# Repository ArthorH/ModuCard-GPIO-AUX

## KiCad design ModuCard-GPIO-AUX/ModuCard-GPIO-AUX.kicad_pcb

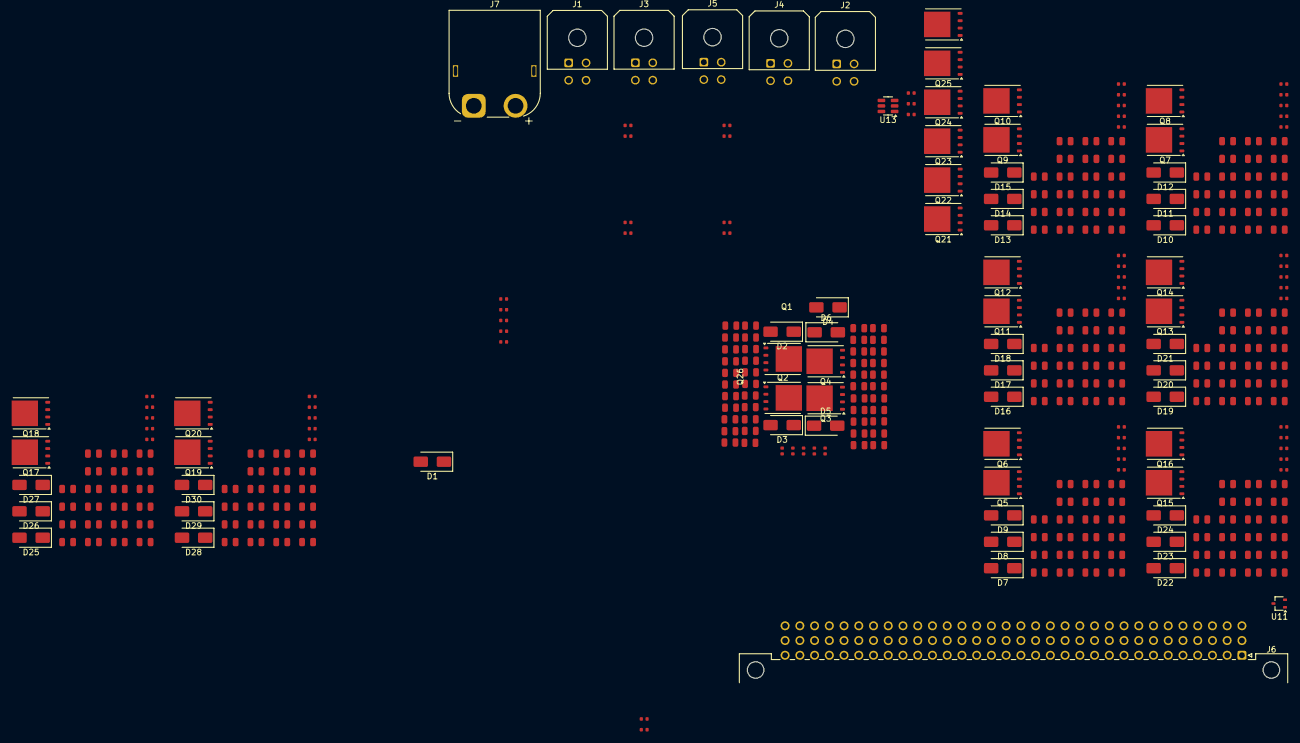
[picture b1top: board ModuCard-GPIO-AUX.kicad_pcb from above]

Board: 2 copper layers, 348 parts (0 on the bottom side), 159 nets, no tracks yet.

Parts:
C1, C2, C3, C4, C5, C6, C7, C8, C9, C10, C11, C12, C13, C14, C15, C16, C17, C18, C19, C20, C21, C22, C23, C24, C25, C26, C27, C28, C29, C30, C31, C32, C33, C34, C35, C36, C37, C38, C39, C40, C41, C42, C43, C44, C45, C46, C47, C48, C49, C50, C51, C52, C53, C54, C55, C56, C57, C58, C59, C60, C61, C62, C63, C64, C65, C66, C67, C68, C69, C70, C71, C72, C73, C74, C75, C76, C77, C78, C79, C80, C81, C82, C83, C84, C85, C86, C87, C88, C89, C90, C91, C92, C93, C94, C95, C96, C97, C98, C99, C100, C101, C102, C103, C104, C105, C106, C107, C108, C109, C110, C111, C112, C113, C114, C115, C116, C117, C118, C119, C120, C121, C122, C123, C124, C125, C126, C127, C128, C129, C130, C131, C132, C133, C134, C135, C136, C137, C138, C139, C140, C141, C142, C143, C144, C145, C146, C147, C148, C149, C150, C151, C152, C153, C154, C155, C156, C157, C158, C159, C160, C161, C162, C163, C164, C165, C166, C167, C168, C169, C170, C171, C172, C173, C174, C175, C176, C177, C178, C179, C180, C181, C182, C183, C184, C185, C186, C187, C188, C189, C190, C191, C192, C193, C194, C195, C196, C197, C198, C199, C200, C201, C202, C203, C204, C205, C206, C207, C208, C209, C210, C211, C212, C213, C214, C215, C216, C217, C218, C219, C220: 10uF; C_0805
C222, C223: 100nF; C_0402
D1, D2, D3, D4, D5, D6, D7, D8, D9, D10, D11, D12, D13, D14, D15, D16, D17, D18, D19, D20, D21, D22, D23, D24, D25, D26, D27, D28, D29, D30: SS38; D_SMA
J1, J2, J3, J4, J5: Molex_Micro-Fit_3.0 2x2; Molex_Micro-Fit_3.0_43045-0400_2x02_P3.00mm_Horizontal
J6: 09031967921; DIN41612_R_3x32_Female_Horizontal_THT
J7: AMASS XT60; AMASS_XT60PW-M_1x02_P7.20mm_Horizontal
Q1, Q2, Q3, Q4, Q5, Q6, Q7, Q8, Q9, Q10, Q11, Q12, Q13, Q14, Q15, Q16, Q17, Q18, Q19, Q20, Q21, Q22, Q23, Q24, Q25, Q26: XR30N06F; TDSON-8-1
R1, R13, R25, R37, R49: 1kΩ; R_0402
R2, R3, R4, R5, R6, R7, R8, R9, R10, R11, R12, R14, R15, R16, R17, R18, R19, R20, R21, R22, R23, R24, R26, R27, R28, R29, R30, R31, R32, R33, R34, R35, R36, R38, R39, R40, R41, R42, R43, R44, R45, R46, R47, R48, R50, R51, R52, R53, R54, R55, R56, R57, R58, R59, R60, R61: 10kΩ; R_0402
U11: TPD2E2U06DCK; SOT-323_SC-70
U13: LM74700; SOT-23-6

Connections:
+5V: J1.4, J2.4, J3.4, J4.4, J5.4
+5V_STDBY: J6.a3, J6.b3, J6.c3
+12V: J6.a11, J6.a12, J6.b11, J6.b12, J6.c11, J6.c12
+24V: J6.a14, J6.b14, J6.c14
/Conn1/A_OUT: R1.2, R2.2
/Conn1/HalfBridge1/OUT: C44.2, D5.2 (A), D6.1 (K), J1.2, Q3.1 (S), Q3.2 (S), Q3.3 (S), Q4.5 (D)
/Conn1/HalfBridge/OUT: C22.2, D2.2 (A), D3.1 (K), J1.1, Q1.1 (S), Q1.2 (S), Q1.3 (S), Q2.5 (D)
/Conn2/A_OUT: R13.2, R14.2
/Conn2/HalfBridge1/OUT: C66.2, D8.2 (A), D9.1 (K), J2.2, Q5.1 (S), Q5.2 (S), Q5.3 (S), Q6.5 (D)
/Conn2/HalfBridge/OUT: C88.2, D11.2 (A), D12.1 (K), J2.1, Q7.1 (S), Q7.2 (S), Q7.3 (S), Q8.5 (D)
/Conn3/A_OUT: R25.2, R26.2
/Conn3/HalfBridge1/OUT: C110.2, D14.2 (A), D15.1 (K), J3.2, Q9.1 (S), Q9.2 (S), Q9.3 (S), Q10.5 (D)
/Conn3/HalfBridge/OUT: C132.2, D17.2 (A), D18.1 (K), J3.1, Q11.1 (S), Q11.2 (S), Q11.3 (S), Q12.5 (D)
/Conn4/A_OUT: R37.2, R38.2
/Conn4/HalfBridge1/OUT: C154.2, D20.2 (A), D21.1 (K), J4.2, Q13.1 (S), Q13.2 (S), Q13.3 (S), Q14.5 (D)
/Conn4/HalfBridge/OUT: C176.2, D23.2 (A), D24.1 (K), J4.1, Q15.1 (S), Q15.2 (S), Q15.3 (S), Q16.5 (D)
/Conn5/A_OUT: R49.2, R50.2
/Conn5/HalfBridge1/OUT: C198.2, D26.2 (A), D27.1 (K), J5.2, Q17.1 (S), Q17.2 (S), Q17.3 (S), Q18.5 (D)
/Conn5/HalfBridge/OUT: C220.2, D29.2 (A), D30.1 (K), J5.1, Q19.1 (S), Q19.2 (S), Q19.3 (S), Q20.5 (D)
/backplane/BACKPLANE.D+: J6.a2, U11.2
/backplane/BACKPLANE.D-: J6.c2, U11.1
/backplane/CAN1.+: J6.a5, J6.b5, J6.c5
/backplane/CAN1.-: J6.a6, J6.b6, J6.c6
/backplane/CAN2.+: J6.a8, J6.b8, J6.c8
/backplane/CAN2.-: J6.a9, J6.b9, J6.c9
GND: C1.2, C3.2, C5.2, C7.2, C9.2, C11.2, C13.2, C15.2, C17.2, C19.2, C21.2, C23.2, C25.2, C27.2, C29.2, C31.2, C33.2, C35.2, C37.2, C39.2, C41.2, C43.2, C45.2, C47.2, C49.2, C51.2, C53.2, C55.2, C57.2, C59.2, C61.2, C63.2, C65.2, C67.2, C69.2, C71.2, C73.2, C75.2, C77.2, C79.2, C81.2, C83.2, C85.2, C87.2, C89.2, C91.2, C93.2, C95.2, C97.2, C99.2, C101.2, C103.2, C105.2, C107.2, C109.2, C111.2, C113.2, C115.2, C117.2, C119.2, C121.2, C123.2, C125.2, C127.2, C129.2, C131.2, C133.2, C135.2, C137.2, C139.2, C141.2, C143.2, C145.2, C147.2, C149.2, C151.2, C153.2, C155.2, C157.2, C159.2, C161.2, C163.2, C165.2, C167.2, C169.2, C171.2, C173.2, C175.2, C177.2, C179.2, C181.2, C183.2, C185.2, C187.2, C189.2, C191.2, C193.2, C195.2, C197.2, C199.2, C201.2, C203.2, C205.2, C207.2, C209.2, C211.2, C213.2, C215.2, C217.2, C219.2, D3.2 (A), D6.2 (A), D9.2 (A), D12.2 (A), D15.2 (A), D18.2 (A), D21.2 (A), D24.2 (A), D27.2 (A), D30.2 (A), J6.a1, J6.a4, J6.a7, J6.a10, J6.a13, J6.a15, J6.a32, J6.b1, J6.b2, J6.b4, J6.b7, J6.b10, J6.b13, J6.b15, J6.b32, J6.c1, J6.c4, J6.c7, J6.c10, J6.c13, J6.c15, J6.c32, J7.1, Q2.1 (S), Q2.2 (S), Q2.3 (S), Q4.1 (S), Q4.2 (S), Q4.3 (S), Q6.1 (S), Q6.2 (S), Q6.3 (S), Q8.1 (S), Q8.2 (S), Q8.3 (S), Q10.1 (S), Q10.2 (S), Q10.3 (S), Q12.1 (S), Q12.2 (S), Q12.3 (S), Q14.1 (S), Q14.2 (S), Q14.3 (S), Q16.1 (S), Q16.2 (S), Q16.3 (S), Q18.1 (S), Q18.2 (S), Q18.3 (S), Q20.1 (S), Q20.2 (S), Q20.3 (S), R2.1, R5.1, R10.1, R14.1, R17.1, R22.1, R26.1, R29.1, R34.1, R38.1, R41.1, R46.1, R50.1, R53.1, R58.1, U11.3, U13.2 (GND)
unnamed: C2.2, C3.1
unnamed: C4.2, C5.1
unnamed: C6.2, C7.1
unnamed: C8.2, C9.1
unnamed: C10.2, C11.1
unnamed: C12.2, C13.1
unnamed: C14.2, C15.1
unnamed: C16.2, C17.1
unnamed: C18.2, C19.1
unnamed: C20.2, C21.1
unnamed: C24.2, C25.1
unnamed: C26.2, C27.1
unnamed: C28.2, C29.1
unnamed: C30.2, C31.1
unnamed: C32.2, C33.1
unnamed: C34.2, C35.1
unnamed: C36.2, C37.1
unnamed: C38.2, C39.1
unnamed: C40.2, C41.1
unnamed: C42.2, C43.1
unnamed: C46.2, C47.1
unnamed: C48.2, C49.1
unnamed: C50.2, C51.1
unnamed: C52.2, C53.1
unnamed: C54.2, C55.1
unnamed: C56.2, C57.1
unnamed: C58.2, C59.1
unnamed: C60.2, C61.1
unnamed: C62.2, C63.1
unnamed: C64.2, C65.1
unnamed: C68.2, C69.1
unnamed: C70.2, C71.1
unnamed: C72.2, C73.1
unnamed: C74.2, C75.1
unnamed: C76.2, C77.1
unnamed: C78.2, C79.1
unnamed: C80.2, C81.1
unnamed: C82.2, C83.1
unnamed: C84.2, C85.1
unnamed: C86.2, C87.1
unnamed: C90.2, C91.1
unnamed: C92.2, C93.1
unnamed: C94.2, C95.1
unnamed: C96.2, C97.1
unnamed: C98.2, C99.1
unnamed: C100.2, C101.1
unnamed: C102.2, C103.1
unnamed: C104.2, C105.1
unnamed: C106.2, C107.1
unnamed: C108.2, C109.1
unnamed: C112.2, C113.1
unnamed: C114.2, C115.1
unnamed: C116.2, C117.1
unnamed: C118.2, C119.1
unnamed: C120.2, C121.1
unnamed: C122.2, C123.1
unnamed: C124.2, C125.1
unnamed: C126.2, C127.1
unnamed: C128.2, C129.1
unnamed: C130.2, C131.1
unnamed: C134.2, C135.1
unnamed: C136.2, C137.1
unnamed: C138.2, C139.1
unnamed: C140.2, C141.1
unnamed: C142.2, C143.1
unnamed: C144.2, C145.1
unnamed: C146.2, C147.1
unnamed: C148.2, C149.1
unnamed: C150.2, C151.1
unnamed: C152.2, C153.1
unnamed: C156.2, C157.1
unnamed: C158.2, C159.1
unnamed: C160.2, C161.1
unnamed: C162.2, C163.1
unnamed: C164.2, C165.1
unnamed: C166.2, C167.1
unnamed: C168.2, C169.1
unnamed: C170.2, C171.1
unnamed: C172.2, C173.1
unnamed: C174.2, C175.1
unnamed: C178.2, C179.1
unnamed: C180.2, C181.1
unnamed: C182.2, C183.1
unnamed: C184.2, C185.1
unnamed: C186.2, C187.1
unnamed: C188.2, C189.1
unnamed: C190.2, C191.1
unnamed: C192.2, C193.1
unnamed: C194.2, C195.1
unnamed: C196.2, C197.1
unnamed: C200.2, C201.1
unnamed: C202.2, C203.1
unnamed: C204.2, C205.1
unnamed: C206.2, C207.1
unnamed: C208.2, C209.1
unnamed: C210.2, C211.1
unnamed: C212.2, C213.1
unnamed: C214.2, C215.1
unnamed: C216.2, C217.1
unnamed: C218.2, C219.1
unnamed: C222.1, C223.2
unnamed: J1.3, R1.1
unnamed: J2.3, R13.1
unnamed: J3.3, R25.1
unnamed: J4.3, R37.1
unnamed: J5.3, R49.1
unnamed: C223.1, J7.2, Q21.1 (S), Q21.2 (S), Q21.3 (S), Q22.1 (S), Q22.2 (S), Q22.3 (S), Q23.1 (S), Q23.2 (S), Q23.3 (S), Q24.1 (S), Q24.2 (S), Q24.3 (S), Q25.1 (S), Q25.2 (S), Q25.3 (S), Q26.1 (S), Q26.2 (S), Q26.3 (S), R61.1, U13.6 (ANODE)
unnamed: Q1.4 (G), R6.2
unnamed: Q2.4 (G), R7.2
unnamed: Q3.4 (G), R11.2
unnamed: Q4.4 (G), R12.2
unnamed: Q5.4 (G), R18.2
unnamed: Q6.4 (G), R19.2
unnamed: Q7.4 (G), R23.2
unnamed: Q8.4 (G), R24.2
unnamed: Q9.4 (G), R30.2
unnamed: Q10.4 (G), R31.2
unnamed: Q11.4 (G), R35.2
unnamed: Q12.4 (G), R36.2
unnamed: Q13.4 (G), R42.2
unnamed: Q14.4 (G), R43.2
unnamed: Q15.4 (G), R47.2
unnamed: Q16.4 (G), R48.2
unnamed: Q17.4 (G), R54.2
unnamed: Q18.4 (G), R55.2
unnamed: Q19.4 (G), R59.2
unnamed: Q20.4 (G), R60.2
unnamed: Q21.5 (D), Q22.5 (D), Q23.5 (D), Q24.5 (D), Q25.5 (D), Q26.5 (D), U13.4 (CATHODE)
unnamed: Q21.4 (G), Q22.4 (G), Q23.4 (G), Q24.4 (G), Q25.4 (G), Q26.4 (G), U13.5 (GATE)
unnamed: R61.2, U13.3 (EN)
unnamed: C222.2, U13.1 (VCAP)
VIN_BL: C1.1, C23.1, C45.1, C67.1, C89.1, C111.1, C133.1, C155.1, C177.1, C199.1, D1.2 (A), D4.2 (A), D7.2 (A), D10.2 (A), D13.2 (A), D16.2 (A), D19.2 (A), D22.2 (A), D25.2 (A), D28.2 (A), R3.1, R8.1, R15.1, R20.1, R27.1, R32.1, R39.1, R44.1, R51.1, R56.1
VIN_BRIDGE: C2.1, C4.1, C6.1, C8.1, C10.1, C12.1, C14.1, C16.1, C18.1, C20.1, C24.1, C26.1, C28.1, C30.1, C32.1, C34.1, C36.1, C38.1, C40.1, C42.1, C46.1, C48.1, C50.1, C52.1, C54.1, C56.1, C58.1, C60.1, C62.1, C64.1, C68.1, C70.1, C72.1, C74.1, C76.1, C78.1, C80.1, C82.1, C84.1, C86.1, C90.1, C92.1, C94.1, C96.1, C98.1, C100.1, C102.1, C104.1, C106.1, C108.1, C112.1, C114.1, C116.1, C118.1, C120.1, C122.1, C124.1, C126.1, C128.1, C130.1, C134.1, C136.1, C138.1, C140.1, C142.1, C144.1, C146.1, C148.1, C150.1, C152.1, C156.1, C158.1, C160.1, C162.1, C164.1, C166.1, C168.1, C170.1, C172.1, C174.1, C178.1, C180.1, C182.1, C184.1, C186.1, C188.1, C190.1, C192.1, C194.1, C196.1, C200.1, C202.1, C204.1, C206.1, C208.1, C210.1, C212.1, C214.1, C216.1, C218.1, D2.1 (K), D5.1 (K), D8.1 (K), D11.1 (K), D14.1 (K), D17.1 (K), D20.1 (K), D23.1 (K), D26.1 (K), D29.1 (K), Q1.5 (D), Q3.5 (D), Q5.5 (D), Q7.5 (D), Q9.5 (D), Q11.5 (D), Q13.5 (D), Q15.5 (D), Q17.5 (D), Q19.5 (D)

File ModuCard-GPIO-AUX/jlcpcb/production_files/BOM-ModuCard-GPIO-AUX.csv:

Comment,Designator,Footprint,LCSC,Quantity
10kΩ,"R10,R11,R12,R8,R9",R_0402,C25744,5
10uF,"C1,C10,C11,C12,C13,C14,C15,C16,C17,C18,C19,C2,C20,C21,C22,C23,C24,C25,C26,C27,C28,C29,C3,C30,C31,C32,C33,C34,C35,C36,C37,C38,C39,C4,C40,C41,C42,C43,C44,C5,C6,C7,C8,C9",C_0805,C440198,44
XR30N06F,Q1,TDSON-8-1,,1
SS38,D6,D_SMA,,1
XR30N06F,Q2,TDSON-8-1,,1
SS38,D3,D_SMA,,1
SS38,D5,D_SMA,,1
XR30N06F,Q3,TDSON-8-1,,1
XR30N06F,Q4,TDSON-8-1,,1
SS38,D2,D_SMA,,1
SS38,D4,D_SMA,,1
Molex_Micro-Fit_3.0 2x2,J1,Molex_Micro-Fit_3.0_43045-0400_2x02_P3.00mm_Horizontal,,1
AMASS XT60,J7,AMASS_XT60PW-M_1x02_P7.20mm_Horizontal,,1
Molex_Micro-Fit_3.0 2x2,J5,Molex_Micro-Fit_3.0_43045-0400_2x02_P3.00mm_Horizontal,,1
09031967921,J6,DIN41612_R_3x32_Female_Horizontal_THT,,1
Molex_Micro-Fit_3.0 2x2,J2,Molex_Micro-Fit_3.0_43045-0400_2x02_P3.00mm_Horizontal,,1
Molex_Micro-Fit_3.0 2x2,J4,Molex_Micro-Fit_3.0_43045-0400_2x02_P3.00mm_Horizontal,,1
Molex_Micro-Fit_3.0 2x2,J3,Molex_Micro-Fit_3.0_43045-0400_2x02_P3.00mm_Horizontal,,1

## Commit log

2025-05-27 hbridge done
2025-09-24 Initial project
